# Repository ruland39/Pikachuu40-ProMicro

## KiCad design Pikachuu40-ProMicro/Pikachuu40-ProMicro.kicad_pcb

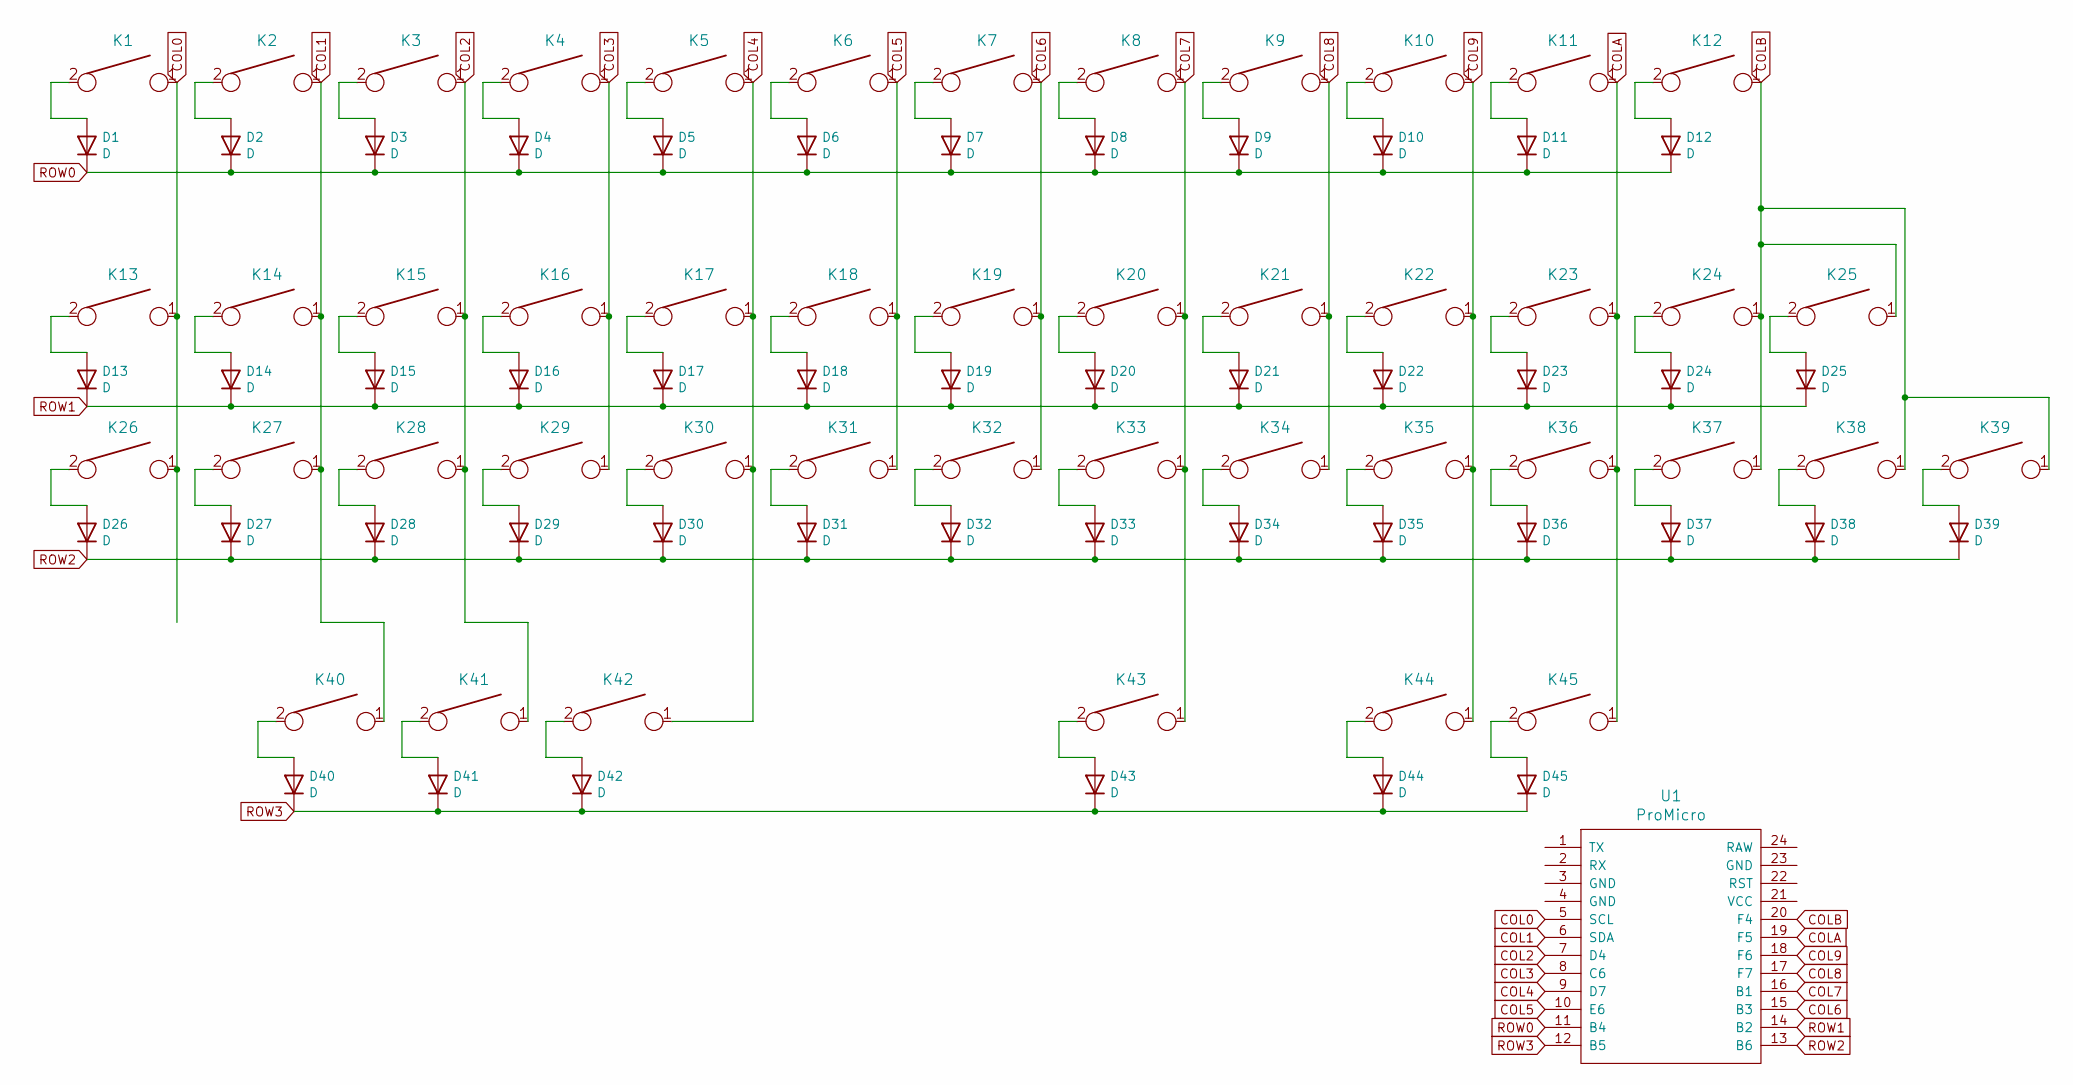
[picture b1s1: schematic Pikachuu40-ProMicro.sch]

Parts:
D1, D2, D3, D4, D5, D6, D7, D8, D9, D10, D11, D12, D13, D14, D15, D16, D17, D18, D19, D20, D21, D22, D23, D24, D25, D26, D27, D28, D29, D30, D31, D32, D33, D34, D35, D36, D37, D38, D39, D40, D41, D42, D43, D44, D45: D; Diode
K1, K2, K3, K4, K5, K6, K7, K8, K9, K10, K11, K12, K13, K14, K15, K16, K17, K18, K19, K20, K21, K22, K23, K24, K25, K26, K27, K28, K29, K30, K31, K32, K33, K34, K35, K36, K37, K38, K39, K40, K41, K42, K43, K44, K45: KEYSW; SW_Cherry_MX_1.00u_PCB
U1: ProMicro; ArduinoProMicro

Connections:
COL0: K1.1, K13.1, K26.1, U1.5 (SCL)
COL1: K2.1, K14.1, K27.1, K40.1, U1.6 (SDA)
COL2: K3.1, K15.1, K28.1, K41.1, U1.7 (D4)
COL3: K4.1, K16.1, K29.1, U1.8 (C6)
COL4: K5.1, K17.1, K30.1, K42.1, U1.9 (D7)
COL5: K6.1, K18.1, K31.1, U1.10 (E6)
COL6: K7.1, K19.1, K32.1, U1.15 (B3)
COL7: K8.1, K20.1, K33.1, K43.1, U1.16 (B1)
COL8: K9.1, K21.1, K34.1, U1.17 (F7)
COL9: K10.1, K22.1, K35.1, K44.1, U1.18 (F6)
COLA: K11.1, K23.1, K36.1, K45.1, U1.19 (F5)
COLB: K12.1, K24.1, K25.1, K37.1, K38.1, K39.1, U1.20 (F4)
unnamed: D1.2 (A), K1.2
unnamed: D2.2 (A), K2.2
unnamed: D3.2 (A), K3.2
unnamed: D4.2 (A), K4.2
unnamed: D5.2 (A), K5.2
unnamed: D6.2 (A), K6.2
unnamed: D7.2 (A), K7.2
unnamed: D8.2 (A), K8.2
unnamed: D9.2 (A), K9.2
unnamed: D10.2 (A), K10.2
unnamed: D11.2 (A), K11.2
unnamed: D12.2 (A), K12.2
unnamed: D13.2 (A), K13.2
unnamed: D14.2 (A), K14.2
unnamed: D15.2 (A), K15.2
unnamed: D16.2 (A), K16.2
unnamed: D17.2 (A), K17.2
unnamed: D18.2 (A), K18.2
unnamed: D19.2 (A), K19.2
unnamed: D20.2 (A), K20.2
unnamed: D21.2 (A), K21.2
unnamed: D22.2 (A), K22.2
unnamed: D23.2 (A), K23.2
unnamed: D24.2 (A), K24.2
unnamed: D25.2 (A), K25.2
unnamed: D26.2 (A), K26.2
unnamed: D27.2 (A), K27.2
unnamed: D28.2 (A), K28.2
unnamed: D29.2 (A), K29.2
unnamed: D30.2 (A), K30.2
unnamed: D31.2 (A), K31.2
unnamed: D32.2 (A), K32.2
unnamed: D33.2 (A), K33.2
unnamed: D34.2 (A), K34.2
unnamed: D35.2 (A), K35.2
unnamed: D36.2 (A), K36.2
unnamed: D37.2 (A), K37.2
unnamed: D38.2 (A), K38.2
unnamed: D39.2 (A), K39.2
unnamed: D40.2 (A), K40.2
unnamed: D41.2 (A), K41.2
unnamed: D42.2 (A), K42.2
unnamed: D43.2 (A), K43.2
unnamed: D44.2 (A), K44.2
unnamed: D45.2 (A), K45.2
ROW0: D1.1 (K), D2.1 (K), D3.1 (K), D4.1 (K), D5.1 (K), D6.1 (K), D7.1 (K), D8.1 (K), D9.1 (K), D10.1 (K), D11.1 (K), D12.1 (K), U1.11 (B4)
ROW1: D13.1 (K), D14.1 (K), D15.1 (K), D16.1 (K), D17.1 (K), D18.1 (K), D19.1 (K), D20.1 (K), D21.1 (K), D22.1 (K), D23.1 (K), D24.1 (K), D25.1 (K), U1.14 (B2)
ROW2: D26.1 (K), D27.1 (K), D28.1 (K), D29.1 (K), D30.1 (K), D31.1 (K), D32.1 (K), D33.1 (K), D34.1 (K), D35.1 (K), D36.1 (K), D37.1 (K), D38.1 (K), D39.1 (K), U1.13 (B6)
ROW3: D40.1 (K), D41.1 (K), D42.1 (K), D43.1 (K), D44.1 (K), D45.1 (K), U1.12 (B5)

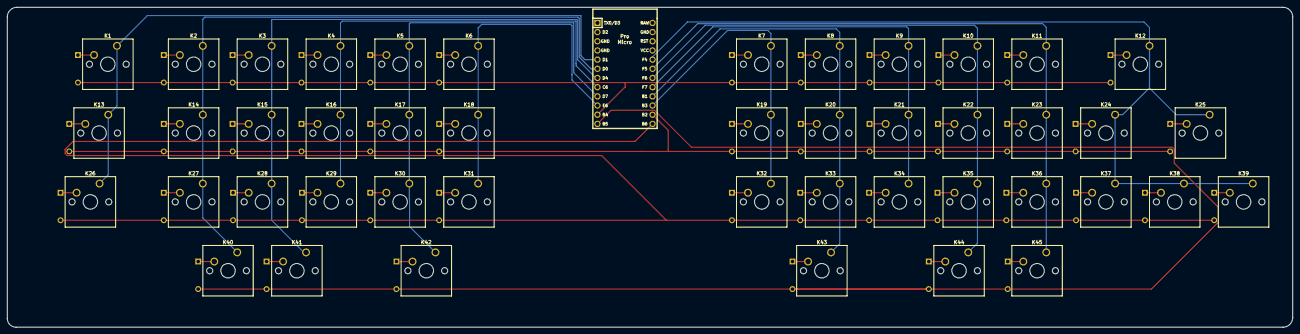
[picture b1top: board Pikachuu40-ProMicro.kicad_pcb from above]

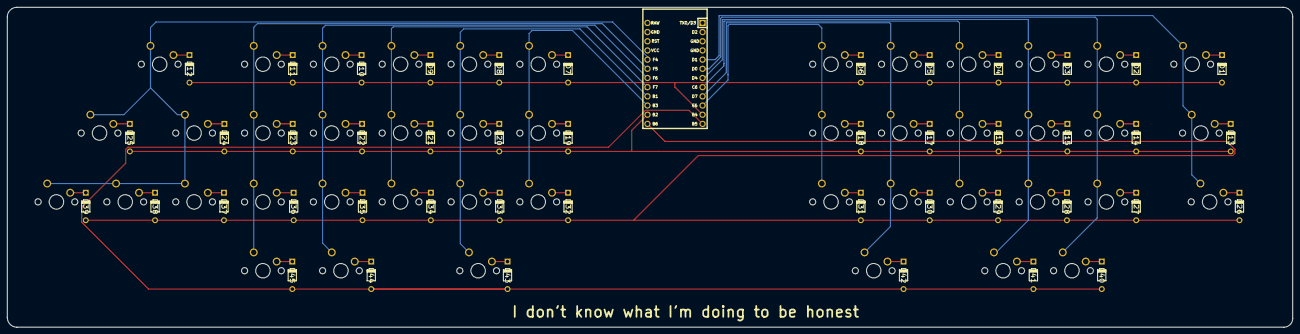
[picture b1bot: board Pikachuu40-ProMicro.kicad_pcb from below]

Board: 2 copper layers, 355.7 x 88.5 mm, 91 parts (45 on the bottom side), 61 nets.

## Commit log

2021-07-15 Added Library
2021-07-15 Wiring Row Column
2021-07-15 Schematic done
2021-07-15 Schematic done again
2021-07-16 Rough Routing Done
